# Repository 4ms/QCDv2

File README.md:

QCD firmware version 2.1

Works on all PCB v2.x

Changelog:
v2.1
Calibration mode to set Div/Mult detent positions

v2.0.1
Bug fixed to sync clock outputs

v2.0
Updated for ATMEGA328 chip

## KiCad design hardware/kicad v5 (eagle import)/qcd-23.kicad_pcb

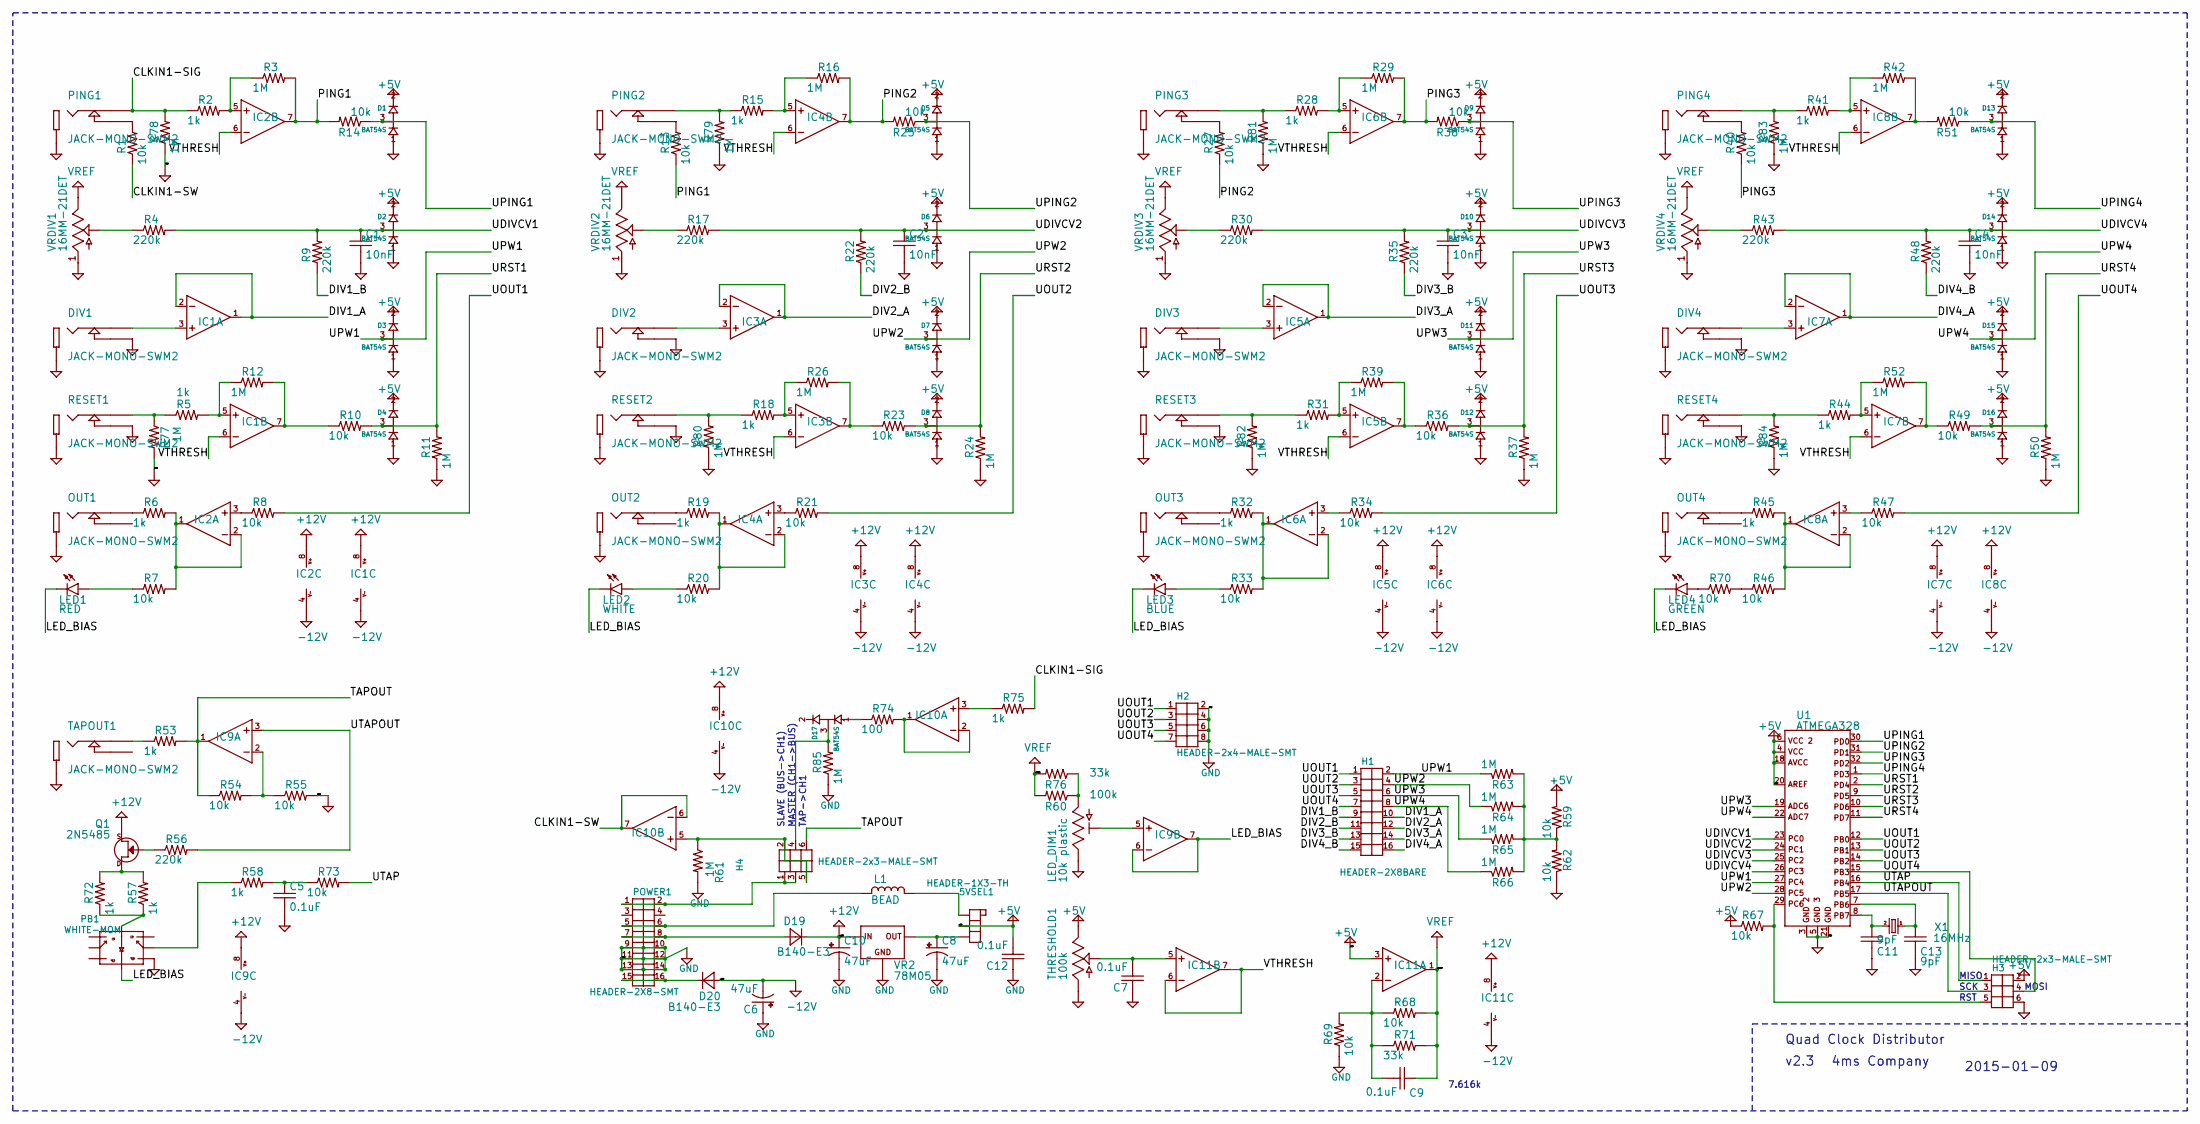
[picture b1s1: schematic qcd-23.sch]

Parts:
5VSEL1: HEADER-1X3-TH
C1, C2, C3, C4: 10nF; C0603
C5, C7, C9, C12: 0.1uF; C0603
C6, C8, C10: 47uF; C-POL-5
C11, C13: 9pF; C0603
D1, D2, D3, D4, D5, D6, D7, D8, D9, D10, D11, D12, D13, D14, D15, D16, D17: BAT54S; SOT23
D19, D20: B140-E3; SMA
DIV1, DIV2, DIV3, DIV4: JACK-MONO-SWM2; PJ301M-12-FIX
H1: HEADER-2X8BARE; HEADER-2X8-SMT
H2: HEADER-2x4-MALE-SMT; HEADER-2X4-SMT
H3, H4: HEADER-2x3-MALE-SMT; HEADER-2X3-SMT
IC1, IC2, IC3, IC4, IC5, IC6, IC7, IC8, IC9, IC10, IC11: TL072; TSSOP8
L1: BEAD; 0603
LED1: RED; LED-T1
LED2: WHITE; LED-T1
LED3: BLUE; LED-T1
LED4: GREEN; LED-T1
LED_DIM1: 10k plastic; TRIM-T73YE
OUT1, OUT2, OUT3, OUT4: JACK-MONO-SWM2; PJ301M-12-FIX
PB1: WHITE-MOM; BUTTON-LED-PB61303
PING1, PING2, PING3, PING4: JACK-MONO-SWM2; PJ301M-12-FIX
POWER1: HEADER-2X8-SMT
Q1: 2N5485; SOT23
R1, R7, R8, R10, R13, R14, R20, R21, R23, R25, R27, R33, R34, R36, R38, R40, R46, R47, R49, R51, R54, R55, R59, R62, R67, R68, R69, R70, R73: 10k; R0603
R2, R5, R6, R15, R18, R19, R28, R31, R32, R41, R44, R45, R53, R57, R58, R72, R75: 1k; R0603
R3, R11, R12, R16, R24, R26, R29, R37, R39, R42, R50, R52, R61, R63, R64, R65, R66, R77, R78, R79, R80, R81, R82, R83, R84, R85: 1M; R0603
R4, R9, R17, R22, R30, R35, R43, R48, R56: 220k; R0603
R60: 100k; R0603
R71, R76: 33k; R0603
R74: 100; R0603
RESET1, RESET2, RESET3, RESET4: JACK-MONO-SWM2; PJ301M-12-FIX
TAPOUT1: JACK-MONO-SWM2; PJ301M-12-FIX
THRESHOLD1: 100k; PIHER-6MM
U1: ATMEGA328; TQFP-32
VR2: 78M05; DPAK
VRDIV1, VRDIV2, VRDIV3, VRDIV4: 16MM-21DET; 16MM-RV16AF-4A
X1: 16MHz; FA-238

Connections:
+5V: 5VSEL1.P$2, C12.2, D1.2 (CATHODE), D2.2 (CATHODE), D3.2 (CATHODE), D4.2 (CATHODE), D5.2 (CATHODE), D6.2 (CATHODE), D7.2 (CATHODE), D8.2 (CATHODE), D9.2 (CATHODE), D10.2 (CATHODE), D11.2 (CATHODE), D12.2 (CATHODE), D13.2 (CATHODE), D14.2 (CATHODE), D15.2 (CATHODE), D16.2 (CATHODE), H3.2, IC11.3 (+IN), R59.2, R67.1, THRESHOLD1.3, U1.4, U1.6, U1.18, U1.20
+12V: C10.+, D19.K (C), IC1.8 (V+), IC2.8 (V+), IC3.8 (V+), IC4.8 (V+), IC5.8 (V+), IC6.8 (V+), IC7.8 (V+), IC8.8 (V+), IC9.8 (V+), IC10.8 (V+), IC11.8 (V+), Q1.2 (S), VR2.1 (IN)
+VREF: C9.1, IC11.1 (OUT), R60.2, R68.2, R71.2, R76.2, VRDIV1.3, VRDIV2.3, VRDIV3.3, VRDIV4.3
-12V: C6.-, D20.A, IC1.4 (V-), IC2.4 (V-), IC3.4 (V-), IC4.4 (V-), IC5.4 (V-), IC6.4 (V-), IC7.4 (V-), IC8.4 (V-), IC9.4 (V-), IC10.4 (V-), IC11.4 (V-)
/CLKIN1-SIG: PING1.1 (TIP), R2.1, R75.2, R78.2
/CLKIN1-SW: IC10.6 (-IN), IC10.7 (OUT), R1.1
/DIV1_A: H1.10, IC1.1 (OUT), IC1.2 (-IN)
/DIV1_B: H1.9, R9.1
/DIV2_A: H1.12, IC3.1 (OUT), IC3.2 (-IN)
/DIV2_B: H1.11, R22.1
/DIV3_A: H1.14, IC5.1 (OUT), IC5.2 (-IN)
/DIV3_B: H1.13, R35.1
/DIV4_A: H1.16, IC7.1 (OUT), IC7.2 (-IN)
/DIV4_B: H1.15, R48.1
/LED_BIAS: IC9.6 (-IN), IC9.7 (OUT), LED1.K (C), LED2.K (C), LED3.K (C), LED4.K (C), PB1.P$8
/PING1: IC2.7 (OUT), R3.2, R13.1, R14.2
/PING2: IC4.7 (OUT), R16.2, R25.2, R27.1
/PING3: IC6.7 (OUT), R29.2, R38.2, R40.1
/TAPOUT: H4.6, IC9.1 (OUT), R53.2, R54.1
/UDIVCV1: C1.1, D2.3 (COMMON), R4.2, R9.2, U1.23
/UDIVCV2: C2.1, D6.3 (COMMON), R17.2, R22.2, U1.24
/UDIVCV3: C3.1, D10.3 (COMMON), R30.2, R35.2, U1.25
/UDIVCV4: C4.1, D14.3 (COMMON), R43.2, R48.2, U1.26
/UOUT1: H1.1, H2.1, R8.2, U1.12
/UOUT2: H1.3, H2.3, R21.2, U1.13
/UOUT3: H1.5, H2.5, R34.2, U1.14
/UOUT4: H1.7, H2.7, H3.4, R47.2, U1.15
/UPING1: D1.3 (COMMON), R14.1, U1.30
/UPING2: D5.3 (COMMON), R25.1, U1.31
/UPING3: D9.3 (COMMON), R38.1, U1.32
/UPING4: D13.3 (COMMON), R51.1, U1.1
/UPW1: D3.3 (COMMON), H1.2, R63.1, U1.27
/UPW2: D7.3 (COMMON), H1.4, R64.1, U1.28
/UPW3: D11.3 (COMMON), H1.6, R65.1, U1.19
/UPW4: D15.3 (COMMON), H1.8, R66.1, U1.22
/URST1: D4.3 (COMMON), R10.2, R11.2, U1.2
/URST2: D8.3 (COMMON), R23.2, R24.2, U1.9
/URST3: D12.3 (COMMON), R36.2, R37.2, U1.10
/URST4: D16.3 (COMMON), R49.2, R50.2, U1.11
/UTAP: H3.1, R73.2, U1.16
/UTAPOUT: H3.3, IC9.3 (+IN), R56.2, U1.17
/VTHRESH: IC1.6 (-IN), IC2.6 (-IN), IC3.6 (-IN), IC4.6 (-IN), IC5.6 (-IN), IC6.6 (-IN), IC7.6 (-IN), IC8.6 (-IN), IC11.6 (-IN), IC11.7 (OUT)
GND: C1.2, C2.2, C3.2, C4.2, C5.2, C6.+, C7.1, C8.-, C10.-, C11.2, C12.1, C13.2, D1.1 (ANODE), D2.1 (ANODE), D3.1 (ANODE), D4.1 (ANODE), D5.1 (ANODE), D6.1 (ANODE), D7.1 (ANODE), D8.1 (ANODE), D9.1 (ANODE), D10.1 (ANODE), D11.1 (ANODE), D12.1 (ANODE), D13.1 (ANODE), D14.1 (ANODE), D15.1 (ANODE), D16.1 (ANODE), DIV1.2 (SLEEVE), DIV1.3 (TIP-SW), DIV2.2 (SLEEVE), DIV2.3 (TIP-SW), DIV3.2 (SLEEVE), DIV3.3 (TIP-SW), DIV4.2 (SLEEVE), DIV4.3 (TIP-SW), H2.2, H2.4, H2.6, H2.8, H3.6, LED_DIM1.3, OUT1.2 (SLEEVE), OUT2.2 (SLEEVE), OUT3.2 (SLEEVE), OUT4.2 (SLEEVE), PB1.P$6, PING1.2 (SLEEVE), PING2.2 (SLEEVE), PING3.2 (SLEEVE), PING4.2 (SLEEVE), POWER1.9, POWER1.10, POWER1.11, POWER1.12, POWER1.13, POWER1.14, R11.1, R24.1, R37.1, R50.1, R55.2, R61.2, R62.1, R69.1, R77.2, R78.1, R79.1, R80.1, R81.1, R82.1, R83.1, R84.1, R85.1, RESET1.2 (SLEEVE), RESET1.3 (TIP-SW), RESET2.2 (SLEEVE), RESET2.3 (TIP-SW), RESET3.2 (SLEEVE), RESET3.3 (TIP-SW), RESET4.2 (SLEEVE), RESET4.3 (TIP-SW), TAPOUT1.2 (SLEEVE), THRESHOLD1.1, U1.3, U1.5, U1.21, VR2.4 (GND), VRDIV1.1, VRDIV2.1, VRDIV3.1, VRDIV4.1
unnamed: 5VSEL1.P$1, L1.2 (4)
unnamed: 5VSEL1.P$3, C8.+, VR2.3 (OUT)
unnamed: C5.1, R58.2, R73.1
unnamed: C7.2, IC11.5 (+IN), THRESHOLD1.2
unnamed: C9.2, IC11.2 (-IN), R68.1, R69.2, R71.1
unnamed: C11.1, U1.8, X1.3 (2)
unnamed: C13.1, U1.7, X1.1
unnamed: D17.1 (ANODE), R74.1
unnamed: D17.3 (COMMON), H4.4, R85.2
unnamed: D19.A, POWER1.7, POWER1.8
unnamed: D20.K (C), POWER1.15, POWER1.16
unnamed: DIV1.1 (TIP), IC1.3 (+IN)
unnamed: DIV2.1 (TIP), IC3.3 (+IN)
unnamed: DIV3.1 (TIP), IC5.3 (+IN)
unnamed: DIV4.1 (TIP), IC7.3 (+IN)
unnamed: H3.5, R67.2, U1.29
unnamed: H4.1, H4.3, POWER1.1, POWER1.2
unnamed: H4.2, H4.5, IC10.5 (+IN), R61.1
unnamed: IC1.5 (+IN), R5.2, R12.1
unnamed: IC1.7 (OUT), R10.1, R12.2
unnamed: IC2.1 (OUT), IC2.2 (-IN), R6.2, R7.2
unnamed: IC2.3 (+IN), R8.1
unnamed: IC2.5 (+IN), R2.2, R3.1
unnamed: IC3.5 (+IN), R18.2, R26.1
unnamed: IC3.7 (OUT), R23.1, R26.2
unnamed: IC4.1 (OUT), IC4.2 (-IN), R19.2, R20.2
unnamed: IC4.3 (+IN), R21.1
unnamed: IC4.5 (+IN), R15.2, R16.1
unnamed: IC5.5 (+IN), R31.2, R39.1
unnamed: IC5.7 (OUT), R36.1, R39.2
unnamed: IC6.1 (OUT), IC6.2 (-IN), R32.2, R33.2
unnamed: IC6.3 (+IN), R34.1
unnamed: IC6.5 (+IN), R28.2, R29.1
unnamed: IC7.5 (+IN), R44.2, R52.1
unnamed: IC7.7 (OUT), R49.1, R52.2
unnamed: IC8.1 (OUT), IC8.2 (-IN), R45.2, R46.2
unnamed: IC8.3 (+IN), R47.1
unnamed: IC8.5 (+IN), R41.2, R42.1
unnamed: IC8.7 (OUT), R42.2, R51.2
unnamed: IC9.2 (-IN), R54.2, R55.1
unnamed: IC9.5 (+IN), LED_DIM1.2
unnamed: IC10.1 (OUT), IC10.2 (-IN), R74.2
unnamed: IC10.3 (+IN), R75.1
unnamed: L1.1, POWER1.5, POWER1.6
unnamed: LED1.A, R7.1
unnamed: LED2.A, R20.1
unnamed: LED3.A, R33.1
unnamed: LED4.A, R70.1
unnamed: LED_DIM1.1, R60.1, R76.1
unnamed: OUT1.1 (TIP), R6.1
unnamed: OUT2.1 (TIP), R19.1
unnamed: OUT3.1 (TIP), R32.1
unnamed: OUT4.1 (TIP), R45.1
unnamed: PB1.P$5, R58.1
unnamed: PB1.P$7, R57.1, R72.1
unnamed: PING1.3 (TIP-SW), R1.2
unnamed: PING2.1 (TIP), R15.1, R79.2
unnamed: PING2.3 (TIP-SW), R13.2
unnamed: PING3.1 (TIP), R28.1, R81.2
unnamed: PING3.3 (TIP-SW), R27.2
unnamed: PING4.1 (TIP), R41.1, R83.2
unnamed: PING4.3 (TIP-SW), R40.2
unnamed: Q1.1 (D), R57.2, R72.2
unnamed: Q1.3 (G), R56.1
unnamed: R4.1, VRDIV1.2
unnamed: R5.1, R77.1, RESET1.1 (TIP)
unnamed: R17.1, VRDIV2.2
unnamed: R18.1, R80.2, RESET2.1 (TIP)
unnamed: R30.1, VRDIV3.2
unnamed: R31.1, R82.2, RESET3.1 (TIP)
unnamed: R43.1, VRDIV4.2
unnamed: R44.1, R84.2, RESET4.1 (TIP)
unnamed: R46.1, R70.2
unnamed: R53.1, TAPOUT1.1 (TIP)
unnamed: R59.1, R62.2, R63.2, R64.2, R65.2, R66.2

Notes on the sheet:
MASTER (CH1->BUS)
SLAVE (BUS->CH1)
TAP->CH1
MISO
SCK
RST
MOSI
Quad Clock Distributor
v2.3
4ms Company
2015-01-09
7.616k

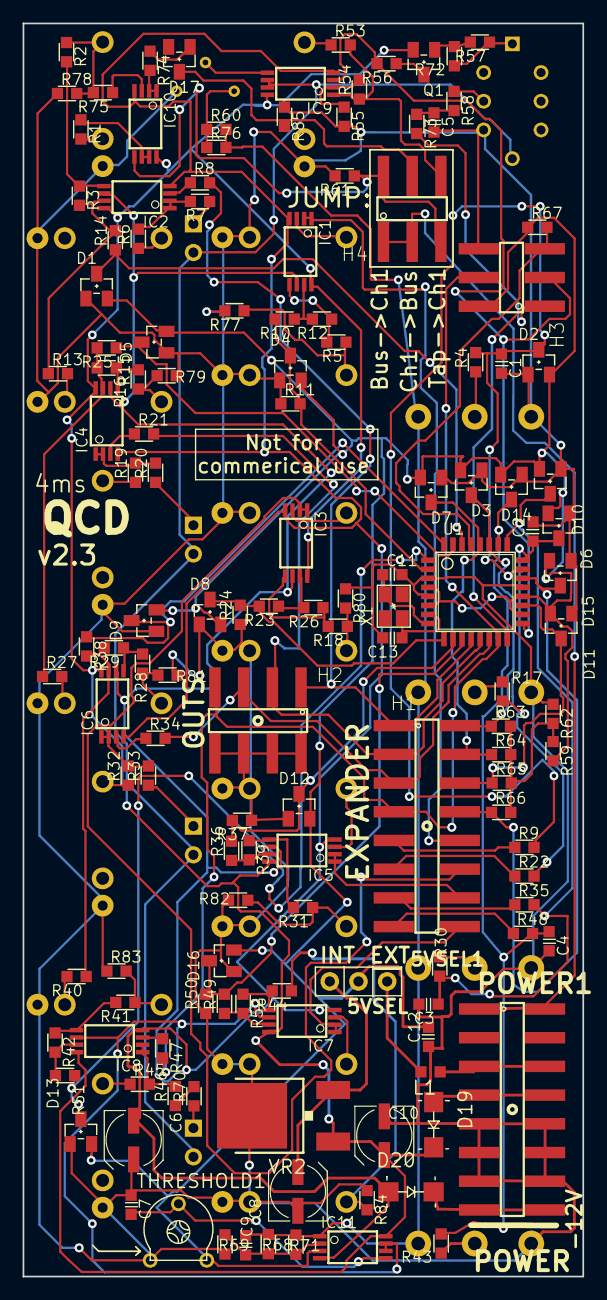
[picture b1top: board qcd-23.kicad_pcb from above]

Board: 2 copper layers, 49.5 x 110.9 mm, 167 parts (0 on the bottom side), 118 nets.

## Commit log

2015-02-06 Beta version. Works on pcb 2.0/2.1.
2015-02-09 in progress
2015-02-09 ADC Values for Vref=1.9*VDD (@VDD=5.0V, Vref=about 9.52)
2015-02-09 in prog
2015-02-11 Release Candidate 1: improved synchronicity for non-reset (jacks fire at same time)
2015-02-11 Release Candidate 1: production (not debug mode)
2015-02-12 Version 1.0: New pot ADC values, tighter Reset timing, adjusted ADC read timing
2017-04-28 Unsure if these changes are valid. Check before production
2017-04-28 added gitignore
2017-06-07 Calibration mode for divmult detent positions
2017-06-07 minor cleanups and comments
2017-06-07 Fixed typo from merging calibration branch
2017-06-08 LED lights work for Calibration mode
2019-02-04 Added hardware files: kicad v5 project, eagle board/sch, and exported schematic as PDF
